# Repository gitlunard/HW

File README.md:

Il progetto è descritto nella cartella hw-doc.
Essendo il progetto giovane, qualcosa potrebbe mancare!!! Aiutaci a completarlo!!!

Per scrivere la documentazione è preferibile utilizzare libreoffice. 
( Lo sappiamo, sull'argomento tool documentazione si apre una discussione infinita...ma abbi pazienza usa libreoffice!)

*********************************************************************************************************************
Se le tue idee, la tua esperienza ed il tuo tempo si comprano con dei soldi allora questo non è il progetto 
che fa per te. Ti consigliamo di lasciar perdere!!!!

Chi ha avviato questo semplice progetto è dell'idea che: 

- Se fai quello che ti piace i soldi non ti servono!!!
- Le idee geniali nascono qunando non ci sono nè pressioni economiche nè pressioni sulle scadenze!!

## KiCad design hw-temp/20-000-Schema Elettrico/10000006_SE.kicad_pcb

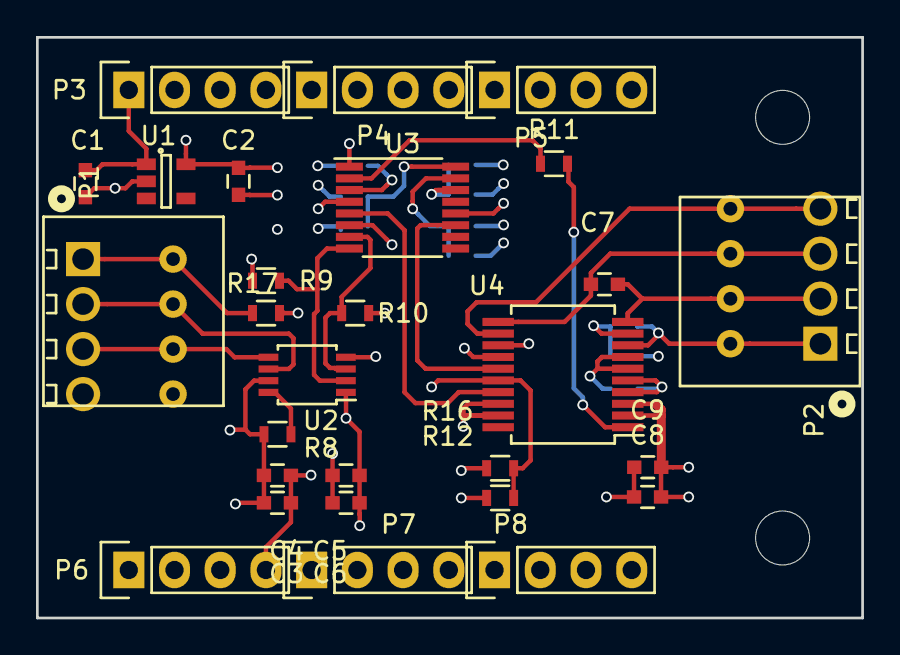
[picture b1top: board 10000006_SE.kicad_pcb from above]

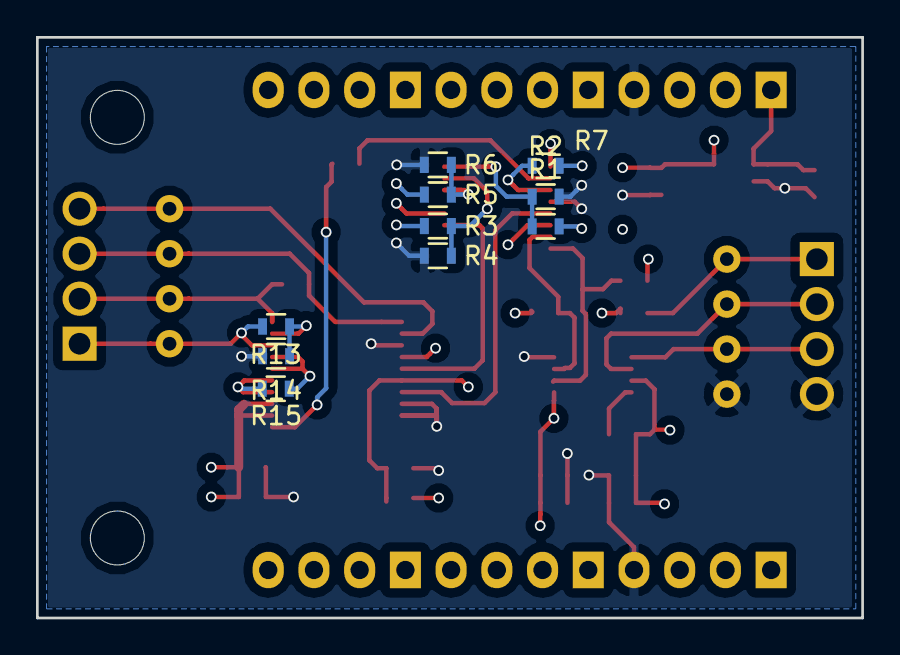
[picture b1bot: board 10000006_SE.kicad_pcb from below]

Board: 4 copper layers, 45.8 x 32.3 mm, 38 parts (10 on the bottom side), 25 nets.

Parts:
C1: C_1u_0603_10_X7R_25V; C_0603
C2: C_3u3_0603_10_X5R_10V; C_0603
C3, C5, C7, C8, C9: C_100n_0603_10_X7R_25V; C_0603
C4, C6: C_100p_0603_5_NP0_50V; C_0603
P1, P2: TERMINAL_01X04_250_RA_SPRING; 1770908
P3, P4, P5, P6, P7, P8: PLUG_01X04_254; Socket_Strip_Straight_1x04
R1, R2, R3, R4, R5, R6, R7, R8, R9, R10, R11, R12, R14, R15, R16: R_10K_0603_5; R_0603
R13: R_402_0603_1; R_0603
R17: R_0_0603_5; R_0603
U1: TPS709; SOT-23-5
U2: PCA9306DC; TSSOP-8_3x3mm_Pitch0.65mm
U3: SC18IS602BIPW; TSSOP-16_4.4x5mm_Pitch0.65mm
U4: MAX31865; SSOP-20_5.3x7.2mm_Pitch0.65mm

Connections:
+3V3: C2.1, C5.1, C6.1, C8.1, C9.1, R1.2, R3.2, R5.2, R7.2, R9.2, R10.2, R12.2, R17.1, U1.5, U2.1, U3.12, U4.2, U4.3
+5V: C1.1, C3.1, C4.1, P1.1, P1.5, P3.1, P6.1, R8.2, R17.2, U1.1, U2.7
/BIAS: R13.1, U4.4, U4.5
/DATA_RDYn: R11.2, U4.1
/FORCE2: R14.2, R15.2, U4.9
/FORCE_N: P2.4, P2.8, U4.12
/FORCE_P: P2.1, P2.5, R14.1, U4.8
/GPIO0: R12.1, R16.2, U3.1, U4.16
/GPIO1: R11.1, U3.2
/I2C_SCL: P1.2, P1.6, P3.2, P6.2, U2.6
/I2C_SCL_3V3: R9.1, U2.2, U3.8
/I2C_SDA: P1.3, P1.7, P3.3, P6.3, U2.5
/I2C_SDA_3V3: R10.1, U2.3, U3.7
/ISENSOR: R13.2, U4.6, U4.7
/RTDIN_N: C7.2, P2.3, P2.7, U4.11
/RTDIN_P: C7.1, P2.2, P2.6, U4.10
/SPI_CLK: U3.11, U4.15
/SPI_MISO: U3.5, U4.17
/SPI_MOSI: U3.6, U4.14
GND: C1.2, C2.2, C3.2, C4.2, C5.2, C6.2, C8.2, C9.2, P1.4, P1.8, P3.4, P6.4, R2.1, R4.1, R6.1, R15.1, R16.1, U1.2, U2.4, U3.4, U4.13, U4.18, U4.19
unnamed: R1.1, R2.2, U3.16
unnamed: R3.1, R4.2, U3.15
unnamed: R5.1, R6.2, U3.14
unnamed: R7.1, U3.3
unnamed: R8.1, U2.8

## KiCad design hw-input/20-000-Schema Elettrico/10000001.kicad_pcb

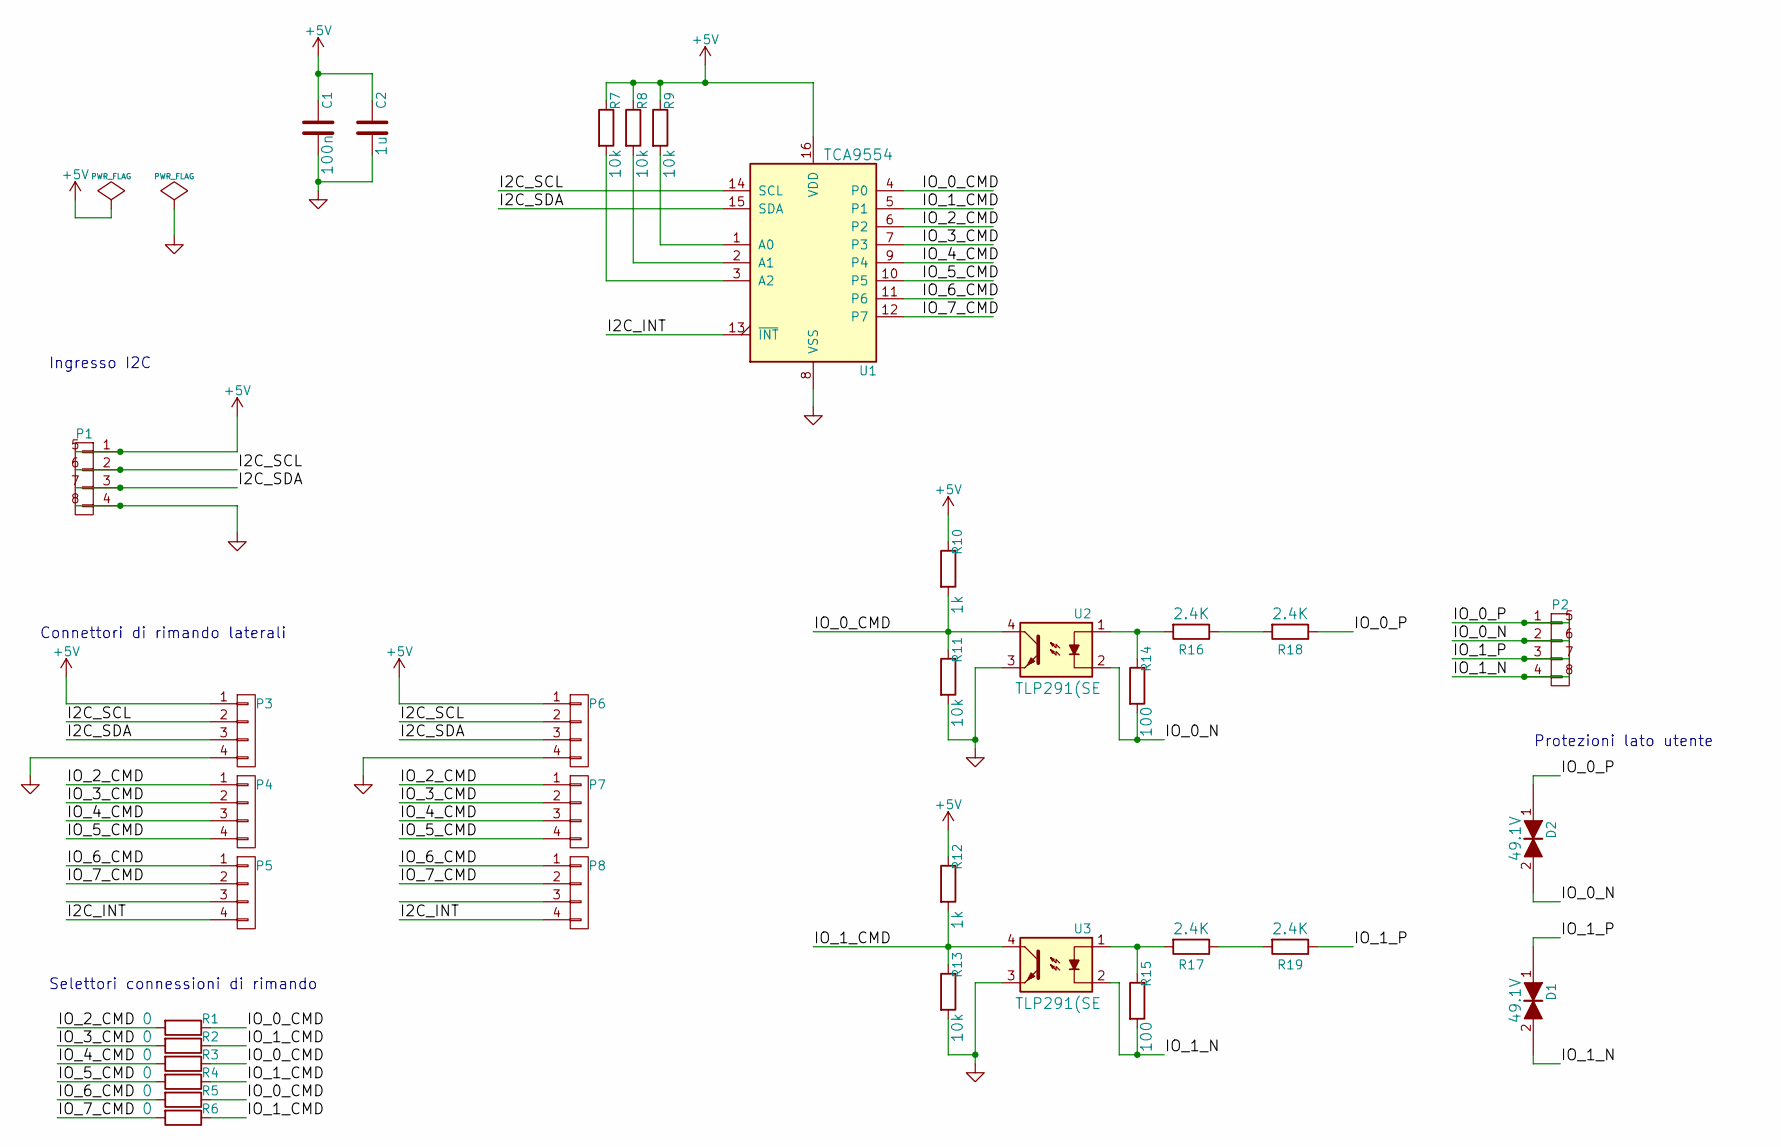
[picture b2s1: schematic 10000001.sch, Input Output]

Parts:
C1: C_100n_0603_10_X7R_25V; C_0603; VOLTAGE 25V
C2: C_1u_0603_10_X7R_25V; C_0603; VOLTAGE 25V
D1, D2: TVS_SMC_49.1V; SMC_Standard
P1, P2: TERMINAL_01X04_250_RA_SPRING; 1770908
P3, P4, P5, P6, P7, P8: PLUG_01X04_254; Socket_Strip_Straight_1x04
R1, R2, R3, R4, R5, R6: R_0_0603_5; R_0603
R7, R8, R9, R11, R13: R_10K_0603_5; R_0603
R10, R12: R_1K_0603_5; R_0603
R14, R15: R_100_0603_5; R_0603
R16, R17, R18, R19: R_2K4_1206_5; R_1206
U1: TCA9554; SSOP-16_3.9x4.9mm_Pitch0.635mm
U2, U3: TLP291(SE; TLP291

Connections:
+5V: C1.1, C2.1, P1.1, P1.5, P3.1, P6.1, R7.1, R8.1, R9.1, R10.1, R12.1, U1.16 (VDD)
/I2C_INT: P5.4, P8.4, U1.13 (~INT~)
/I2C_SCL: P1.2, P1.6, P3.2, P6.2, U1.14 (SCL)
/I2C_SDA: P1.3, P1.7, P3.3, P6.3, U1.15 (SDA)
/IO_0_CMD: R1.1, R3.1, R5.1, R10.2, R11.1, U1.4 (P0), U2.4
/IO_0_N: D1.2, P2.2, P2.6, R14.2, U2.2
/IO_0_P: D1.1, P2.1, P2.5, R18.1
/IO_1_CMD: R2.1, R4.1, R6.1, R12.2, R13.1, U1.5 (P1), U3.4
/IO_1_N: D2.2, P2.4, P2.8, R15.2, U3.2
/IO_1_P: D2.1, P2.3, P2.7, R19.1
/IO_2_CMD: P4.1, P7.1, R1.2, U1.6 (P2)
/IO_3_CMD: P4.2, P7.2, R2.2, U1.7 (P3)
/IO_4_CMD: P4.3, P7.3, R3.2, U1.9 (P4)
/IO_5_CMD: P4.4, P7.4, R4.2, U1.10 (P5)
/IO_6_CMD: P5.1, P8.1, R5.2, U1.11 (P6)
/IO_7_CMD: P5.2, P8.2, R6.2, U1.12 (P7)
GND: C1.2, C2.2, P1.4, P1.8, P3.4, P6.4, R11.2, R13.2, U1.8 (VSS), U2.3, U3.3
unnamed: R7.2, U1.3 (A2)
unnamed: R8.2, U1.2 (A1)
unnamed: R9.2, U1.1 (A0)
unnamed: R14.1, R16.2, U2.1
unnamed: R15.1, R17.2, U3.1
unnamed: R16.1, R18.2
unnamed: R17.1, R19.2

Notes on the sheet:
Ingresso I2C
Connettori di rimando laterali
Selettori connessioni di rimando
Protezioni lato utente

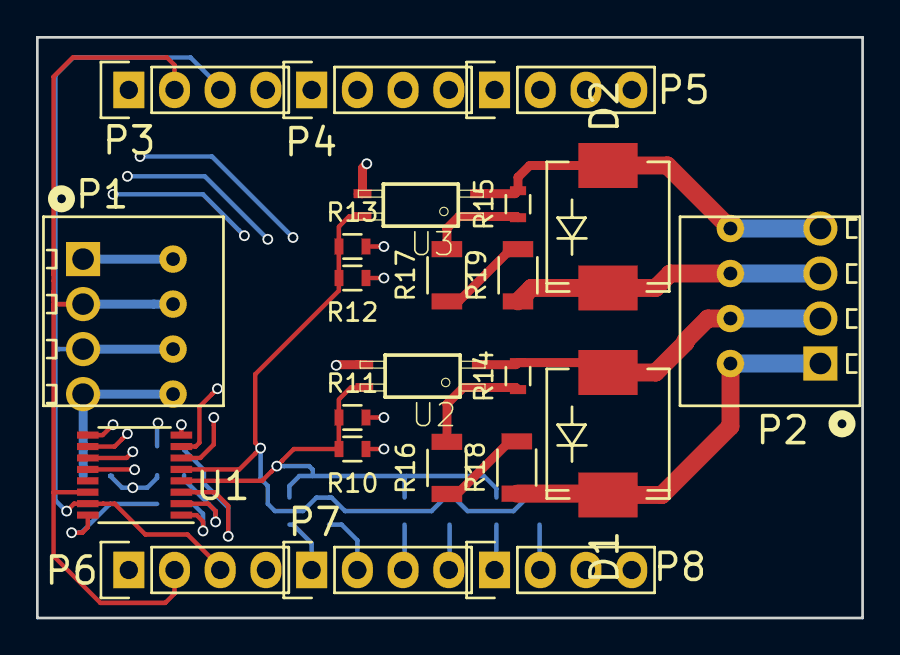
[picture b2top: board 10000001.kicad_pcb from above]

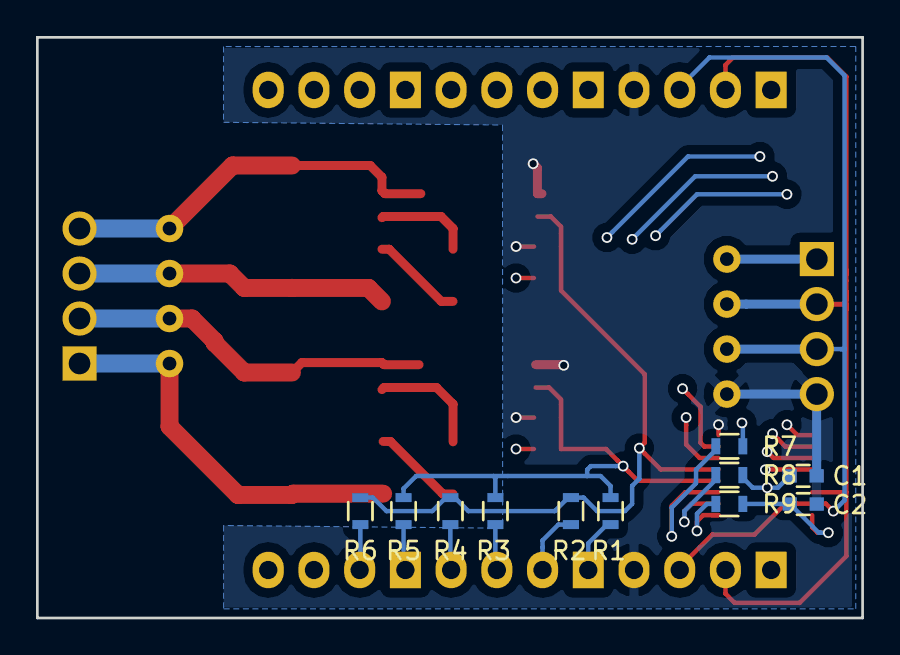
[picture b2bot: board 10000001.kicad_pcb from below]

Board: 4 copper layers, 45.8 x 32.3 mm, 34 parts (11 on the bottom side), 24 nets.

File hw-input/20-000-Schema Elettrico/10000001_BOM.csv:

Source:,C:/progetti_20/OpenS/HW/hw-input/20-000-Schema Elettrico/10000001.sch
Date:,02/09/2016 09:24:14
Tool:,Eeschema 4.0.3-stable
Generator:,C:/programmi_20/KiCad/bin/scripting/plugins/bom_csv_grouped_by_value.py
Component Count:,34

Individual Components:

Item,Qty,Reference(s),Value,LibPart,Footprint,Datasheet,CERAMIC,MF,MF_PN,NOPOP,VAL,VALUE,VOLTAGE,Value
,,C1,C_100n_0603_10_X7R_25V,os_capacitor_SMD:C_100n_0603_10_X7R_25V,Capacitors_SMD:C_0603,,X7R,Murata,GRM188R71E104KA01D,0,,100n,25V,C_100n_0603_10_X7R_25V
,,C2,C_1u_0603_10_X7R_25V,os_capacitor_SMD:C_1u_0603_10_X7R_25V,Capacitors_SMD:C_0603,,X7R,Murata,GRJ188R71E105KE11D,0,,1u,25V,C_1u_0603_10_X7R_25V
,,D1,TVS_SMC_49.1V,tvs:TVS_SMC_49.1V,Diodes_SMD:SMC_Standard,,,BOURNS,SMLJ40CA,0,,,,49.1V
,,D2,TVS_SMC_49.1V,tvs:TVS_SMC_49.1V,Diodes_SMD:SMC_Standard,,,BOURNS,SMLJ40CA,0,,,,49.1V
,,P1,PLUG_01X04_254,os_conn_strip:PLUG_01X04_254,Socket_Strips:Socket_Strip_Straight_1x04,,,Harwin,M20-7820446,0,M20-7820446,,,PLUG_01X04_254
,,P2,PLUG_01X04_254,os_conn_strip:PLUG_01X04_254,Socket_Strips:Socket_Strip_Straight_1x04,,,Harwin,M20-7820446,0,M20-7820446,,,PLUG_01X04_254
,,P3,PLUG_01X04_254,os_conn_strip:PLUG_01X04_254,Socket_Strips:Socket_Strip_Straight_1x04,,,Harwin,M20-7820446,0,M20-7820446,,,PLUG_01X04_254
,,P4,PLUG_01X04_254,os_conn_strip:PLUG_01X04_254,Socket_Strips:Socket_Strip_Straight_1x04,,,Harwin,M20-7820446,0,M20-7820446,,,PLUG_01X04_254
,,P5,PLUG_01X04_254,os_conn_strip:PLUG_01X04_254,Socket_Strips:Socket_Strip_Straight_1x04,,,Harwin,M20-7820446,0,M20-7820446,,,PLUG_01X04_254
,,P6,PLUG_01X04_254,os_conn_strip:PLUG_01X04_254,Socket_Strips:Socket_Strip_Straight_1x04,,,Harwin,M20-7820446,0,M20-7820446,,,PLUG_01X04_254
,,P7,PLUG_01X04_254,os_conn_strip:PLUG_01X04_254,Socket_Strips:Socket_Strip_Straight_1x04,,,Harwin,M20-7820446,0,M20-7820446,,,PLUG_01X04_254
,,P8,PLUG_01X04_254,os_conn_strip:PLUG_01X04_254,Socket_Strips:Socket_Strip_Straight_1x04,,,Harwin,M20-7820446,0,M20-7820446,,,PLUG_01X04_254
,,R1,R_0_0603_5,os_resistor_SMD:R_0_0603_5,Resistors_SMD:R_0603,,,KOA Spear,RK73Z1JTTD,0,0,,,R_0_0603_5
,,R2,R_0_0603_5,os_resistor_SMD:R_0_0603_5,Resistors_SMD:R_0603,,,KOA Spear,RK73Z1JTTD,0,0,,,R_0_0603_5
,,R3,R_0_0603_5,os_resistor_SMD:R_0_0603_5,Resistors_SMD:R_0603,,,KOA Spear,RK73Z1JTTD,0,0,,,R_0_0603_5
,,R4,R_0_0603_5,os_resistor_SMD:R_0_0603_5,Resistors_SMD:R_0603,,,KOA Spear,RK73Z1JTTD,0,0,,,R_0_0603_5
,,R5,R_0_0603_5,os_resistor_SMD:R_0_0603_5,Resistors_SMD:R_0603,,,KOA Spear,RK73Z1JTTD,0,0,,,R_0_0603_5
,,R6,R_0_0603_5,os_resistor_SMD:R_0_0603_5,Resistors_SMD:R_0603,,,KOA Spear,RK73Z1JTTD,0,0,,,R_0_0603_5
,,R7,R_10K_0603_5,os_resistor_SMD:R_10K_0603_5,Resistors_SMD:R_0603,,,KOA Spear,RK73B1JTTD103J,0,10k,,,R_10K_0603_5
,,R8,R_10K_0603_5,os_resistor_SMD:R_10K_0603_5,Resistors_SMD:R_0603,,,KOA Spear,RK73B1JTTD103J,0,10k,,,R_10K_0603_5
,,R9,R_10K_0603_5,os_resistor_SMD:R_10K_0603_5,Resistors_SMD:R_0603,,,KOA Spear,RK73B1JTTD103J,0,10k,,,R_10K_0603_5
,,R10,R_1K_0603_5,os_resistor_SMD:R_1K_0603_5,Resistors_SMD:R_0603,,,KOA Spear,RK73B1JTTD102J,0,1k,,,R_1K_0603_5
,,R11,R_10K_0603_5,os_resistor_SMD:R_10K_0603_5,Resistors_SMD:R_0603,,,KOA Spear,RK73B1JTTD103J,0,10k,,,R_10K_0603_5
,,R12,R_1K_0603_5,os_resistor_SMD:R_1K_0603_5,Resistors_SMD:R_0603,,,KOA Spear,RK73B1JTTD102J,0,1k,,,R_1K_0603_5
,,R13,R_10K_0603_5,os_resistor_SMD:R_10K_0603_5,Resistors_SMD:R_0603,,,KOA Spear,RK73B1JTTD103J,0,10k,,,R_10K_0603_5
,,R14,R_100_0603_5,os_resistor_SMD:R_100_0603_5,Resistors_SMD:R_0603,,,KOA Spear,RK73B1JTTD101J,0,100,,,R_100_0603_5
,,R15,R_100_0603_5,os_resistor_SMD:R_100_0603_5,Resistors_SMD:R_0603,,,KOA Spear,RK73B1JTTD101J,0,100,,,R_100_0603_5
,,R16,R_2K4_1206_5,os_resistor_SMD:R_2K4_1206_5,Resistors_SMD:R_1206,,,KOA Spear,RK73B2BTTD242J,0,2.4K,,,R_2K4_1206_5
,,R17,R_2K4_1206_5,os_resistor_SMD:R_2K4_1206_5,Resistors_SMD:R_1206,,,KOA Spear,RK73B2BTTD242J,0,2.4K,,,R_2K4_1206_5
,,R18,R_2K4_1206_5,os_resistor_SMD:R_2K4_1206_5,Resistors_SMD:R_1206,,,KOA Spear,RK73B2BTTD242J,0,2.4K,,,R_2K4_1206_5
,,R19,R_2K4_1206_5,os_resistor_SMD:R_2K4_1206_5,Resistors_SMD:R_1206,,,KOA Spear,RK73B2BTTD242J,0,2.4K,,,R_2K4_1206_5
,,U1,TCA9554,TI_I2C:TCA9554,Housings_SSOP:SSOP-16_3.9x4.9mm_Pitch0.635mm,,,TI,TCA9554DBQR,0,,,,TCA9554
,,U2,TLP291(SE,os_optocoupler:TLP291(SE,os_optocoupler:TLP291,,,Toshiba,TLP291(SE,0,TLP291(SE,,,TLP291(SE
,,U3,TLP291(SE,os_optocoupler:TLP291(SE,os_optocoupler:TLP291,,,Toshiba,TLP291(SE,0,TLP291(SE,,,TLP291(SE



Collated Components:

Item,Qty,Reference(s),Value,LibPart,Footprint,Datasheet,CERAMIC,MF,MF_PN,NOPOP,VAL,VALUE,VOLTAGE,Value
1,1,C1,C_100n_0603_10_X7R_25V,os_capacitor_SMD:C_100n_0603_10_X7R_25V,Capacitors_SMD:C_0603,,X7R,Murata,GRM188R71E104KA01D,0,,100n,25V,C_100n_0603_10_X7R_25V
2,1,C2,C_1u_0603_10_X7R_25V,os_capacitor_SMD:C_1u_0603_10_X7R_25V,Capacitors_SMD:C_0603,,X7R,Murata,GRJ188R71E105KE11D,0,,1u,25V,C_1u_0603_10_X7R_25V
3,2,"D1, D2",TVS_SMC_49.1V,tvs:TVS_SMC_49.1V,Diodes_SMD:SMC_Standard,,,BOURNS,SMLJ40CA,0,,,,49.1V
4,8,"P1, P2, P3, P4, P5, P6, P7, P8",PLUG_01X04_254,os_conn_strip:PLUG_01X04_254,Socket_Strips:Socket_Strip_Straight_1x04,,,Harwin,M20-7820446,0,M20-7820446,,,PLUG_01X04_254
5,6,"R1, R2, R3, R4, R5, R6",R_0_0603_5,os_resistor_SMD:R_0_0603_5,Resistors_SMD:R_0603,,,KOA Spear,RK73Z1JTTD,0,0,,,R_0_0603_5
6,5,"R7, R8, R9, R11, R13",R_10K_0603_5,os_resistor_SMD:R_10K_0603_5,Resistors_SMD:R_0603,,,KOA Spear,RK73B1JTTD103J,0,10k,,,R_10K_0603_5
7,2,"R10, R12",R_1K_0603_5,os_resistor_SMD:R_1K_0603_5,Resistors_SMD:R_0603,,,KOA Spear,RK73B1JTTD102J,0,1k,,,R_1K_0603_5
8,2,"R14, R15",R_100_0603_5,os_resistor_SMD:R_100_0603_5,Resistors_SMD:R_0603,,,KOA Spear,RK73B1JTTD101J,0,100,,,R_100_0603_5
9,4,"R16, R17, R18, R19",R_2K4_1206_5,os_resistor_SMD:R_2K4_1206_5,Resistors_SMD:R_1206,,,KOA Spear,RK73B2BTTD242J,0,2.4K,,,R_2K4_1206_5
10,1,U1,TCA9554,TI_I2C:TCA9554,Housings_SSOP:SSOP-16_3.9x4.9mm_Pitch0.635mm,,,TI,TCA9554DBQR,0,,,,TCA9554
11,2,"U2, U3",TLP291(SE,os_optocoupler:TLP291(SE,os_optocoupler:TLP291,,,Toshiba,TLP291(SE,0,TLP291(SE,,,TLP291(SE

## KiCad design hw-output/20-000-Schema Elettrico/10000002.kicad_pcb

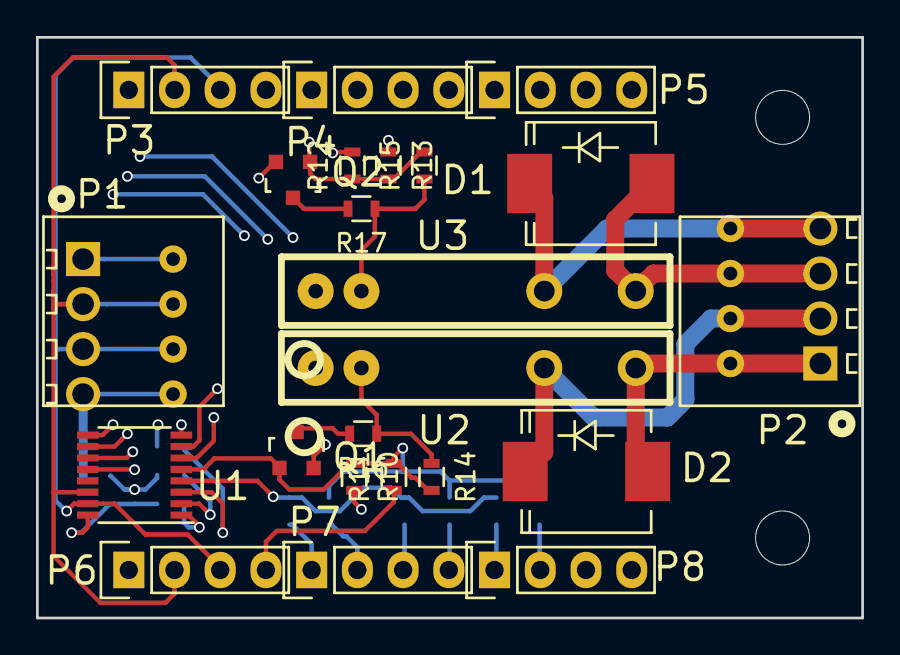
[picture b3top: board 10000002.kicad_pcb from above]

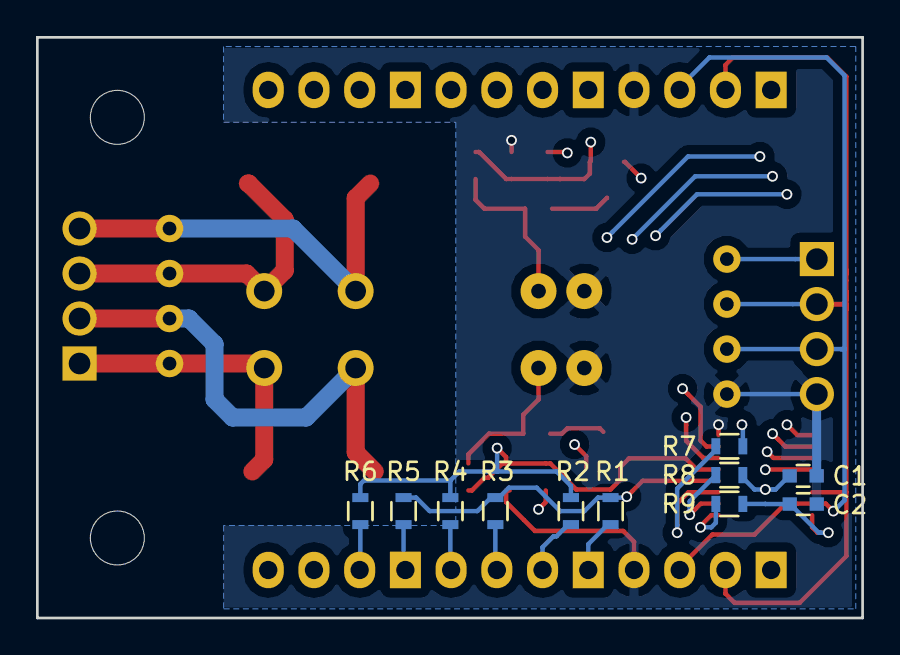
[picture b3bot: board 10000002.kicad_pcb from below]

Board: 4 copper layers, 45.8 x 32.3 mm, 34 parts (11 on the bottom side), 25 nets.

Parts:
C1: C_100n_0603_10_X7R_25V; C_0603
C2: C_1u_0603_10_X7R_25V; C_0603
D1, D2: TVS_SMC_49.1V; SMC_Standard
P1, P2: TERMINAL_01X04_250_RA_SPRING; 1770908
P3, P4, P5, P6, P7, P8: PLUG_01X04_254; Socket_Strip_Straight_1x04
Q1, Q2: Q_PMOS_GSD_BSS84; SOT-23
R1, R2, R3, R4, R5, R6: R_0_0603_5; R_0603
R7, R8, R9, R10, R11, R12, R13: R_10K_0603_5; R_0603
R14, R15, R16, R17: R_1K_0603_5; R_0603
U1: TCA9554; SSOP-16_3.9x4.9mm_Pitch0.635mm
U2, U3: AQZ204; AQZ-SIL-4

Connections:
+5V: C1.1, C2.1, P1.1, P1.5, P3.1, P6.1, Q1.2, Q2.2, R7.2, R8.2, R9.2, R10.2, R12.2, U1.16
/I2C_INT: P5.4, P8.4, U1.13
/I2C_SCL: P1.2, P1.6, P3.2, P6.2, U1.14
/I2C_SDA: P1.3, P1.7, P3.3, P6.3, U1.15
/IO_0_CMD: Q2.1, R1.2, R3.2, R5.2, R12.1, R13.2, R15.2, U1.4
/IO_0_N: D1.2, P2.3, P2.7, U3.4
/IO_0_P: D1.1, P2.4, P2.8, U3.3
/IO_1_CMD: Q1.1, R2.2, R4.2, R6.2, R10.1, R11.2, R14.2, U1.5
/IO_1_N: D2.2, P2.1, P2.5, U2.4
/IO_1_P: D2.1, P2.2, P2.6, U2.3
/IO_2_CMD: P4.1, P7.1, R1.1, U1.6
/IO_3_CMD: P4.2, P7.2, R2.1, U1.7
/IO_4_CMD: P4.3, P7.3, R3.1, U1.9
/IO_5_CMD: P4.4, P7.4, R4.1, U1.10
/IO_6_CMD: P5.1, P8.1, R5.1, U1.11
/IO_7_CMD: P5.2, P8.2, R6.1, U1.12
/NC1: P5.3, P8.3
GND: C1.2, C2.2, P1.4, P1.8, P3.4, P6.4, R11.1, R13.1, U1.8, U2.1, U3.1
unnamed: Q1.3, R16.2
unnamed: Q2.3, R17.2
unnamed: R7.1, U1.3
unnamed: R8.1, U1.2
unnamed: R9.1, U1.1
unnamed: R14.1, R16.1, U2.2
unnamed: R15.1, R17.1, U3.2

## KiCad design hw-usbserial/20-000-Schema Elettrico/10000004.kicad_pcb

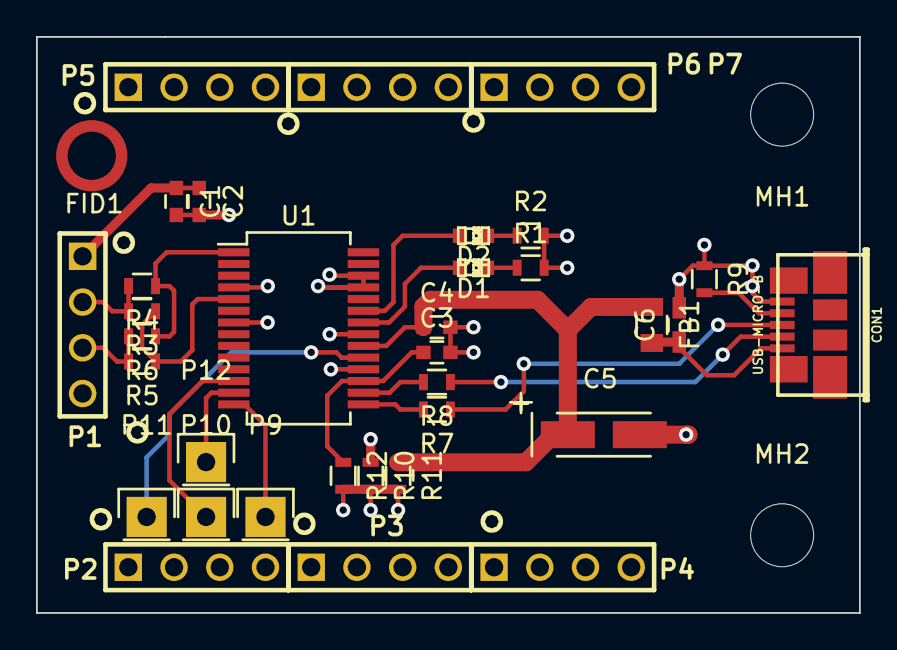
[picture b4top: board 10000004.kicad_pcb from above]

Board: 4 copper layers, 45.7 x 32.0 mm, 37 parts (0 on the bottom side), 23 nets.

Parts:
C1, C3, C4: 100n; C_0603
C2: 1u; C_0603
C5: 4.7u; TantalC_SizeA_EIA-3216_HandSoldering
C6: 10n; C_0603_HandSoldering
CON1: USB-MICRO-B; conn_usb_B_micro_smd
D1, D2: LED; LED-0603
FB1: FILTER; C_0805
FID1: Fiducial_Modern_CopperTop
MH1, MH2: MountingHole_3-5mm
P1, P2, P3, P4, P5, P6, P7: CONN_01X04; PIN_ARRAY_4x1
P9, P10, P11, P12: CONN_01X01; Pin_Header_Straight_1x01
R1, R2: 270; R_0603
R3, R4, R5, R6, R7, R8, R9, R10, R11, R12: 0; R_0603
U1: FT232RL; SSOP-28_5.3x10.2mm_Pitch0.65mm

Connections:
+5V: C4.1, C5.1, FB1.1, R11.1, U1.20
/3V3: C3.1, R12.1, U1.17
/SCH_RX: P1.3, R5.2, R6.2
/SCH_TX: P1.2, R3.2, R4.2
/USBDN: CON1.2, R8.1
/USBDP: CON1.3, R7.1
/VCCIO: R1.2, R2.2, R10.2, R11.2, R12.2, U1.4
GND: C1.2, C2.2, C3.2, C4.2, C5.2, C6.2, CON1.5, P1.4, P2.4, P5.4, R9.1, U1.7, U1.18, U1.21, U1.25, U1.26
unnamed: C6.1, CON1.1, FB1.2
unnamed: CON1.4, R9.2
unnamed: D1.1, R1.1
unnamed: D1.2, U1.22
unnamed: D2.1, R2.1
unnamed: D2.2, U1.23
unnamed: P9.1, U1.14
unnamed: P10.1, U1.12
unnamed: P11.1, U1.19
unnamed: P12.1, U1.13
unnamed: R3.1, R5.1, U1.5
unnamed: R4.1, R6.1, U1.1
unnamed: R7.2, U1.15
unnamed: R8.2, U1.16
VDD: C1.1, C2.1, P1.1, P2.1, P5.1, R10.1

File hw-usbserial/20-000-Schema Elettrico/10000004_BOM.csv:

"Id";"Riferimento";"Contenitore";"Quantità";"Valore";"Produttore";
1;"U1";"SSOP-28_5.3x10.2mm_Pitch0.65mm";1;"FT232RL";;;
2;"P7,P6,P5,P4,P3,P2,P1";"PIN_ARRAY_4x1";7;"CONN_01X04";;;
3;"FID1";"Fiducial_Modern_CopperTop";1;"Fiducial_Modern_CopperTop";;;
4;"MH1,MH2";"MountingHole_3-5mm";2;"MountingHole_3-5mm";;;
5;"C1,C3,C4";"C_0603";3;"100n";;;
6;"C2";"C_0603";1;"1u";;;
7;"C5";"TantalC_SizeA_EIA-3216_HandSoldering";1;"4.7u";;;
8;"C6";"C_0603_HandSoldering";1;"10n";;;
9;"D1,D2";"LED-0603";2;"LED";;;
10;"FB1";"C_0805";1;"FILTER";;;
11;"P9,P10,P11,P12";"Pin_Header_Straight_1x01";4;"CONN_01X01";;;
12;"R1,R2";"R_0603";2;"270";;;
13;"R3,R4,R5,R6,R7,R8,R9,R10,R11,R12";"R_0603";10;"0";;;
14;"CON1";"conn_usb_B_micro_smd";1;"USB-MICRO-B";;;

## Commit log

2014-10-20 Primo commit!
2014-10-23 Commit struttura cartelle e schema vuoto. Commit documenti di descrizione schemi base.
2014-11-01 Terminato albero delle cartelle
2014-11-01 Aggiunto documento di specifica fisica... (forse sto esagerando)
2014-11-01 Aggiunte dimenticanze al documento di specifica fisica
2014-11-02 Aggiunti requisiti
    - Connessione 220V a.c.
    - Ingresso ADC
    - Porta RS232
2014-11-22 Aggiunti documenti di descrizione interfacce RS232, USB e distribuzione alimentazione... manca solo ADC!
2014-11-30 Aggiornato schematico modulo ingressi
2015-01-07 Aggiornato schema
2015-01-26 Aggiornato albero delle directory. Iniziato layout scheda uscite di potenza.
2015-01-31 Terminato sbroglio proliminare scheda uscite. Da impostare regole elettriche di isolamento e portata di corrente per terminare definitivamente. Mancano fiducial e scritte.
2015-02-25 Completamento sbroglio hw-output
2015-02-25 rimosse cartelle in origine
2015-02-25 aggiornamento documenti
2015-03-09 Corretto albero dei documenti, corretto codice dell'unità uscite (era 10000002 nello schema e 10000004 nei documenti, allineato allo schema)
2015-04-17 Scheda input ed output completate con fori di montaggio, fiducial e serigrafie.
2015-04-20 Aggiunte capacità di bypass su alimentazione I2C expander
2015-05-22 Terminato sbroglio convertitore USB seriale.
2015-06-06 Aggiunte librerie - simosio: libreria da linkare direttamente in kicad, ma aggiunta come sottomodulo. - varie: librerie vecchio stile stand-alone da aggiungere direttamente in kicad e da eliminare in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
    Nota, provare a creare un repository di librerie nuovo stile, in cui integrare varie
2015-06-24 Aggiunte librerie special.lib
2015-06-24 Generati file gerber per produzione
2015-07-17 Aggiunto file di pannellizzazione
2015-07-20 Aggiunta BOM
2015-07-22 terminata BOM di acquisti
2015-07-23 aggiornati acquisti
2015-09-07 Aggiunti test report con correzzioni necessarie per i primi test delle schede.
    !! NB !!
    Tutte le PCS sono errate in queste versioni perchè i piani non sono aggiornati e quindi annegato piste e vias creando corti non voluti!!
    !! NB !!
2015-10-13 Aggiunti documenti beagle-board
2015-10-13 Aggiornato documento beagle-board con procedura di creazione SD
2015-10-17 Aggiornata documentazione scheda ingressi e scheda uscite per nuova versione HW.
2015-10-17 Aggiunta prima documentazione scheda misura temperatura
2015-10-20 Aggiunti documenti sensore di temperatura
2015-10-20 aggiunta file di validazione beagle board
2015-10-20 Aggiunti documenti per bridge I2C to SPI
2015-10-24 spostato nel repository utils
2015-11-04 Iniziato schema misura temperatura con PT100
2015-11-18 Commit partizle avanzamento schematico scheda analogica.
2015-11-18 Aggiunti datasheet LDO e level translator per scheda temperatura
2015-12-10 Terminato schema scheda misura temperatura
2016-01-08 Aggiornato schema scheda temperatura a nuova versione kicad. Aggiunti script e librerie per generazione diretta BOM con codici d'ordine.
2016-01-20 aggiornamento completo libreria e schematico per generazione BOM
2016-01-20 Piazzamento scheda iniziato
2016-01-26 Pulizia schema
2016-01-26 Inizio nuovo schema versione 02
2016-01-31 Terminato schema uscite
2016-09-02 Completato schema elettrico con codice produttore
2016-09-02 Completato schema elettrico con codici produttore
2016-09-22 Completato schema e sbroglio
2016-09-22 completato schema elettrico e sbroglio
2016-10-07 Commit definitivo
2016-10-07 PCB terminato
